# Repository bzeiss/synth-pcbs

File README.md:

# synth-pcbs
This site contains some stuff I have built for some synths/samplers I own.

I tinker with electronics, release stuff when I feel like it and I make it public when it's maybe not perfect. I'm not an electronics expert, so I may not always know what I'm doing. I learn the necessary electronics as I use it. Use at your own risk.

Be smart. Don't just trust the stuff I offer for download here. Take a look at the schematic and the PCB design beforehand.

Feedback is always very welcome 😄 Feel free to ask question in the [discussions](https://github.com/bzeiss/synth-pcbs/discussions).

***

The main content of this site (descriptions, documentations) can be found **[in the Wiki](https://github.com/bzeiss/synth-pcbs/wiki)**.

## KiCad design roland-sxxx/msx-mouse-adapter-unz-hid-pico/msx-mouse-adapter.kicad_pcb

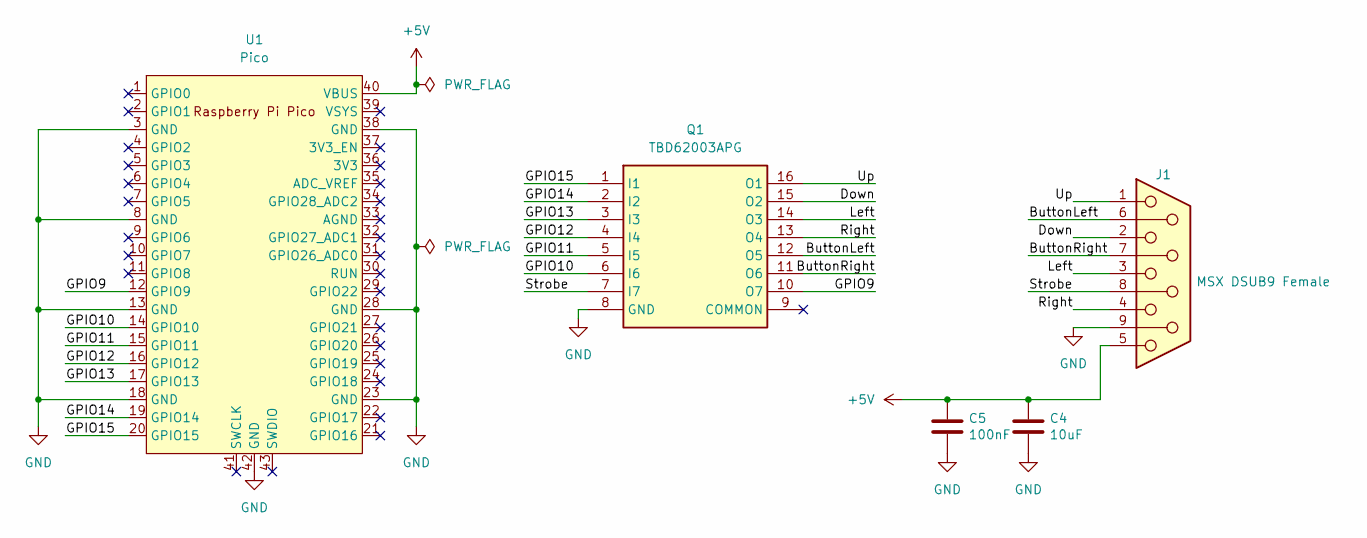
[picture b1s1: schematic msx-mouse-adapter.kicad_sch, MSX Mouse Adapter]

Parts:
C4: 10uF; C_0805_2012Metric_Pad1.18x1.45mm_HandSolder; LCSC C15850
C5: 100nF; C_0805_2012Metric_Pad1.18x1.45mm_HandSolder; LCSC C1525
J1: MSX DSUB9 Female
Q1: TBD62003APG; DIP762W60P254L1975H445Q16N; Mouser Part Number 757-TBD62003APG
U1: Pico; RPi_Pico_SMD_TH

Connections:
+5V: C4.1, C5.1, J1.5, U1.40 (VBUS)
/ButtonLeft: J1.6, Q1.12 (O5)
/ButtonRight: J1.7, Q1.11 (O6)
/Down: J1.2, Q1.15 (O2)
/GPIO9: Q1.10 (O7), U1.12 (GPIO9)
/GPIO10: Q1.6 (I6), U1.14 (GPIO10)
/GPIO11: Q1.5 (I5), U1.15 (GPIO11)
/GPIO12: Q1.4 (I4), U1.16 (GPIO12)
/GPIO13: Q1.3 (I3), U1.17 (GPIO13)
/GPIO14: Q1.2 (I2), U1.19 (GPIO14)
/GPIO15: Q1.1 (I1), U1.20 (GPIO15)
/Left: J1.3, Q1.14 (O3)
/Right: J1.4, Q1.13 (O4)
/Strobe: J1.8, Q1.7 (I7)
/Up: J1.1, Q1.16 (O1)
GND: C4.2, C5.2, J1.9, Q1.8 (GND), U1.3 (GND), U1.8 (GND), U1.13 (GND), U1.18 (GND), U1.23 (GND), U1.28 (GND), U1.38 (GND), U1.42 (GND)

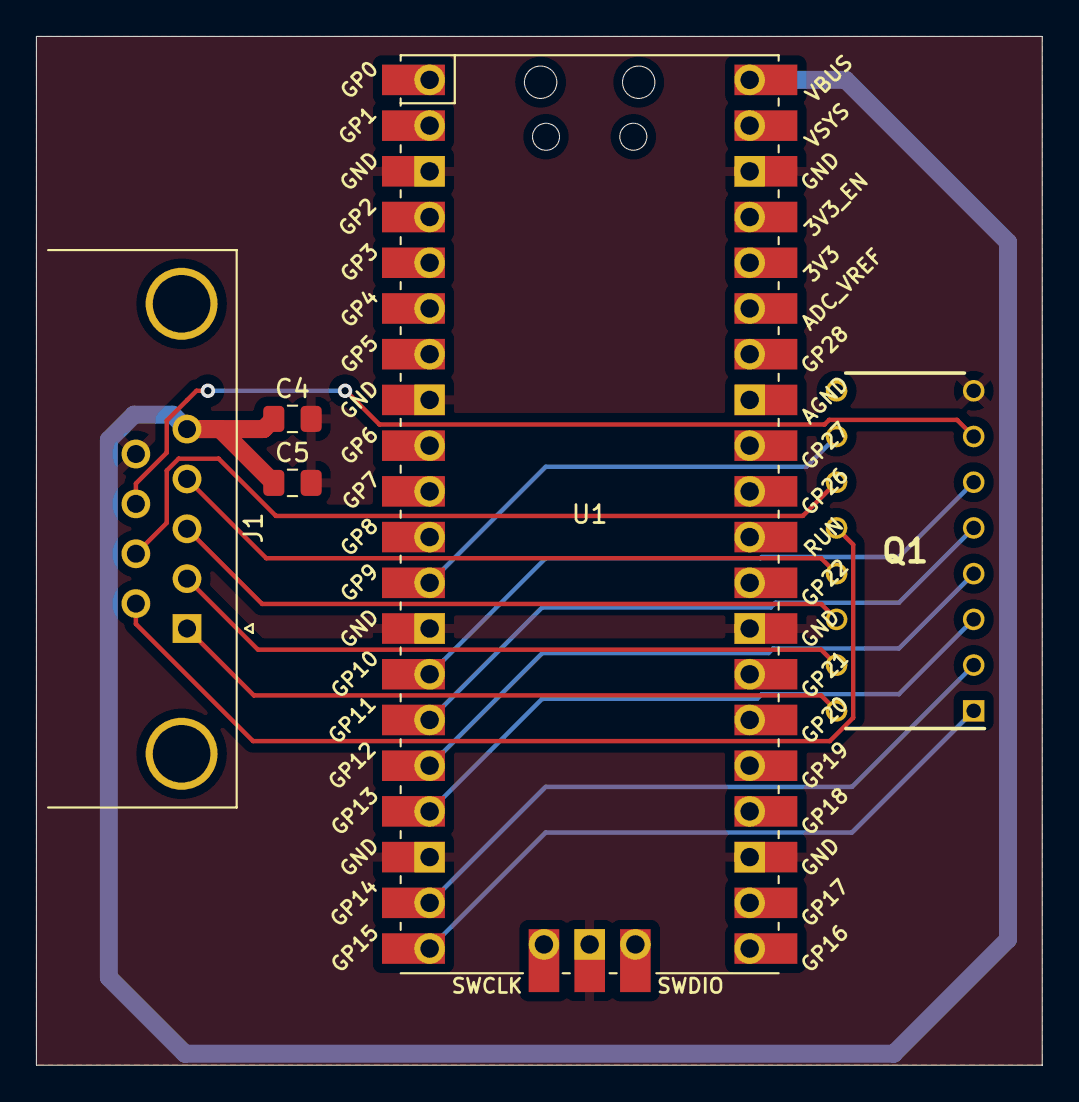
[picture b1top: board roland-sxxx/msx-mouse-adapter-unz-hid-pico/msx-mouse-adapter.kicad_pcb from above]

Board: 2 copper layers, 55.9 x 57.1 mm, 5 parts (0 on the bottom side), 16 nets.

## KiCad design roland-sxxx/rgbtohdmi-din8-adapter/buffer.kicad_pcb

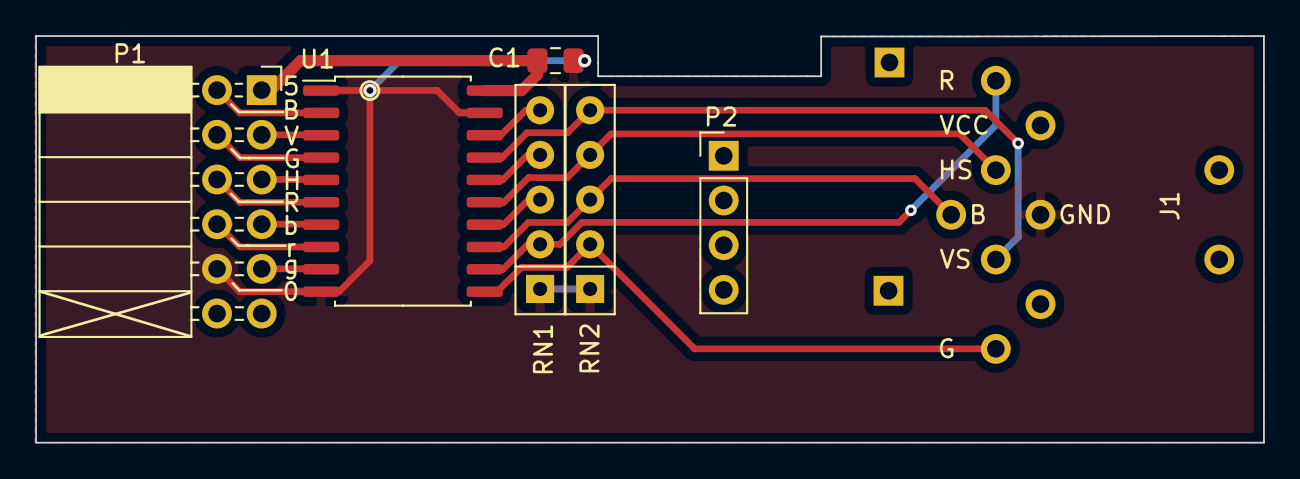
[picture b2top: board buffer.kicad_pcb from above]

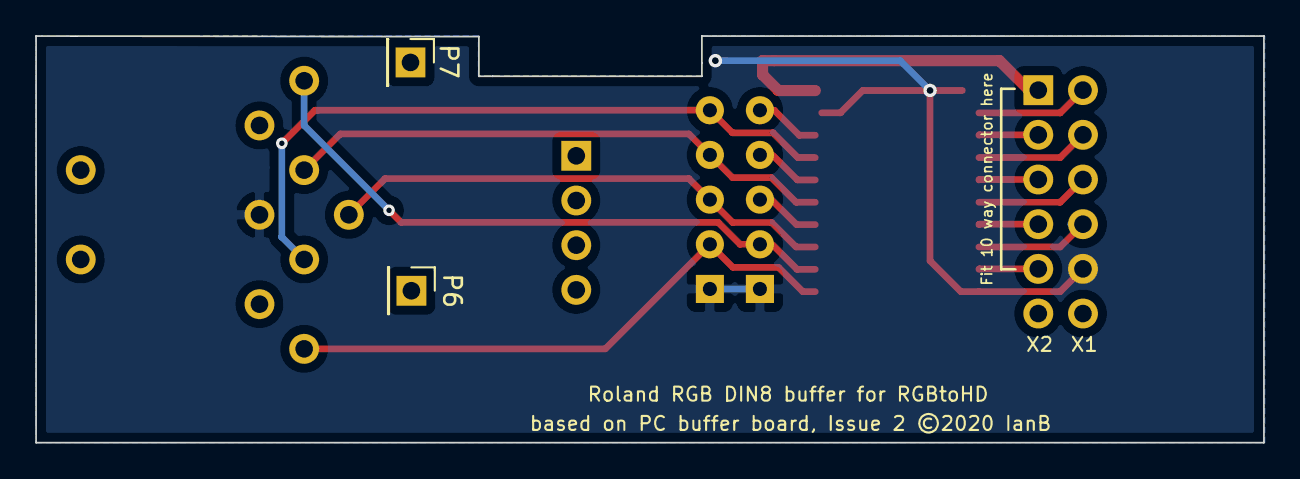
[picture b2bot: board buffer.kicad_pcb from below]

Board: 2 copper layers, 69.8 x 23.1 mm, 9 parts (2 on the bottom side), 18 nets.

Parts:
C1: 100n; C_0805_2012Metric_Pad1.15x1.40mm_HandSolder
J1: DIN-8 Female (Symbol has 2 and 8 swapped!); DIN8_5211511-1
P1: Conn_02x06_Odd_Even; PinSocket_2x06_P2.54mm_Horizontal
P2: Conn_01x04; PinHeader_1x04_P2.54mm_Vertical
P6, P7: Conn_01x01; PinHeader_1x01_P2.54mm_Vertical
RN1, RN2: 470R; R_Array_SIP5
U1: 74LS245; SOIC-20W_7.5x12.8mm_P1.27mm

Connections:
/B2: P1.7, U1.7
/B3: P1.2, U1.2
/G2: P1.9, U1.9
/G3: P1.4, U1.4
/GND: C1.1, J1.2, P1.10, RN1.1, RN2.1, U1.1, U1.10, U1.19
/I_B2: J1.8, RN2.3, U1.13
/I_B3: RN1.5, U1.18
/I_G2: J1.7, RN2.2, U1.11
/I_G3: RN1.4, U1.16
/I_R2: J1.6, RN1.2, U1.12
/I_R3: RN1.3, U1.14
/I_SYNC: J1.4, RN2.4, U1.15
/I_VSYNC: J1.5, RN2.5, U1.17
/R2: P1.8, U1.8
/R3: P1.6, U1.6
/SYNC: P1.5, U1.5
/VCC: C1.2, P1.1, U1.20
/VSYNC: P1.3, U1.3

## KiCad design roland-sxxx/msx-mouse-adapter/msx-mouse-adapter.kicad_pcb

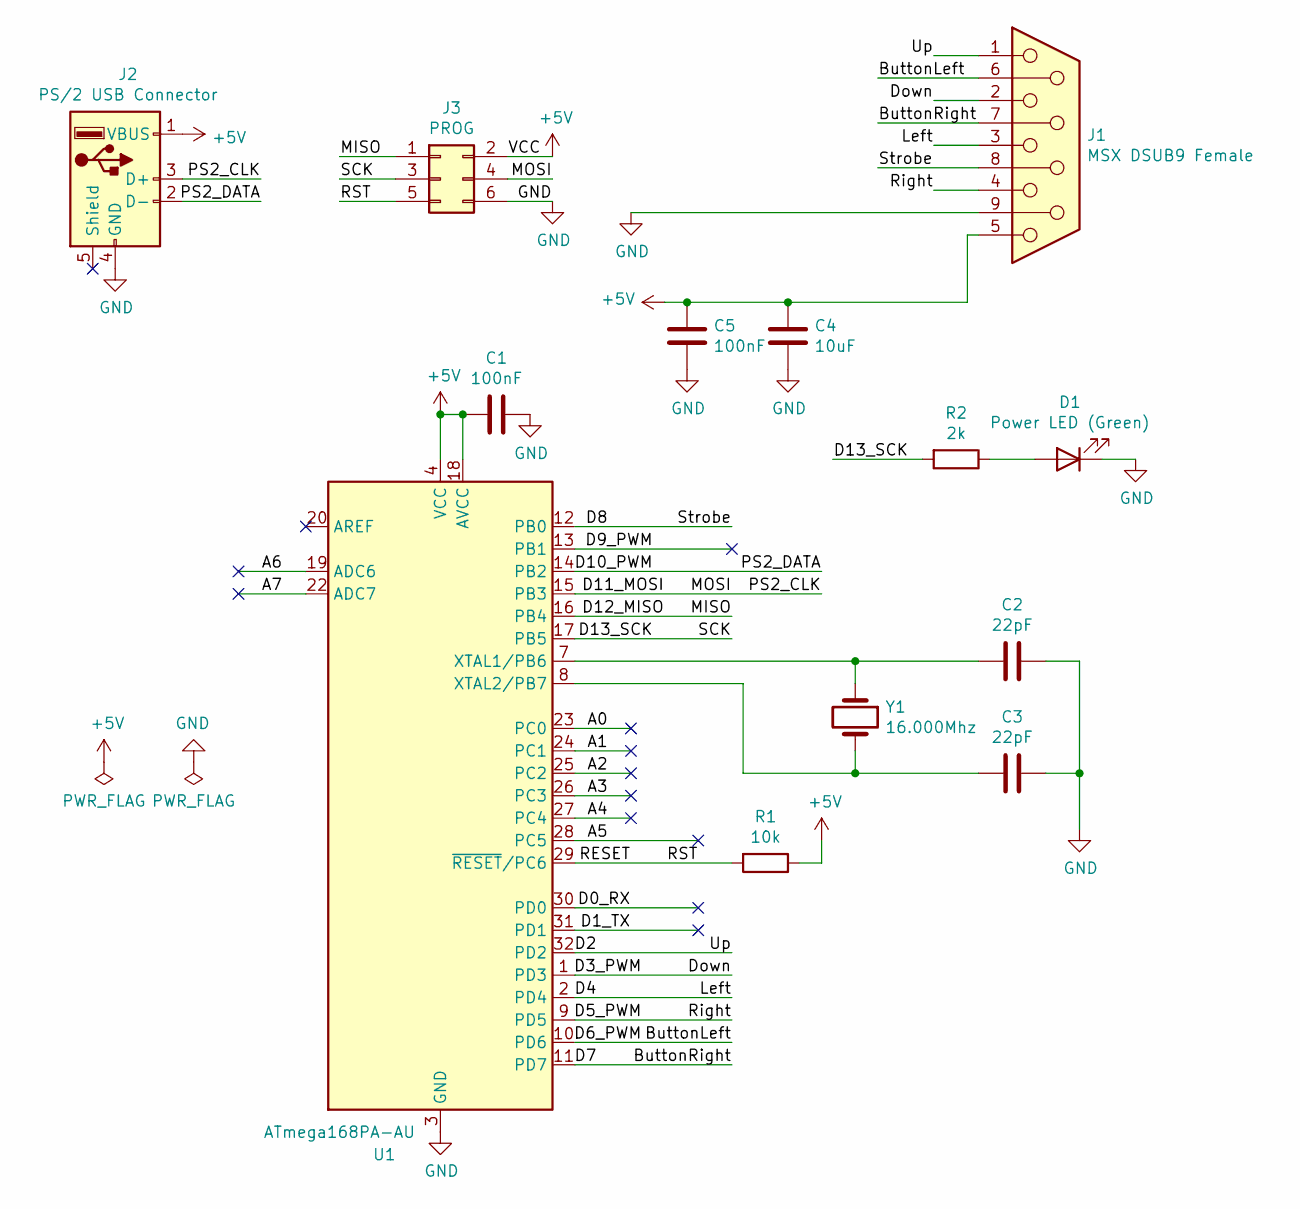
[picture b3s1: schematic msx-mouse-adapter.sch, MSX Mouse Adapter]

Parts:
C1, C5: 100nF; C_0805_2012Metric_Pad1.18x1.45mm_HandSolder; LCSC C1525
C2, C3: 22pF; C_0805_2012Metric_Pad1.18x1.45mm_HandSolder; LCSC C1555
C4: 10uF; C_0805_2012Metric_Pad1.18x1.45mm_HandSolder; LCSC C15850
D1: Power LED (Green); LED_0805_2012Metric_Pad1.15x1.40mm_HandSolder; LCSC C917188
J1: MSX DSUB9 Female
J2: PS/2 USB Connector; USB_A_Molex_67643_Horizontal
J3: PROG; PinHeader_2x03_P2.54mm_Vertical
R1: 10k; R_0805_2012Metric_Pad1.20x1.40mm_HandSolder; LCSC C25744
R2: 2k; R_0805_2012Metric_Pad1.20x1.40mm_HandSolder; LCSC C4109
U1: ATmega168PA-AU; TQFP-32_7x7mm_P0.8mm; LCSC C8728
Y1: 16.000Mhz; Crystal_SMD_7050-4Pin_7.0x5.0mm

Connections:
+5V: C1.2, C4.1, C5.1, J1.5, J2.1 (VBUS), J3.2, R1.1, U1.4 (VCC), U1.6 (VCC), U1.18 (AVCC)
/A0: U1.23 (PC0)
/A1: U1.24 (PC1)
/A2: U1.25 (PC2)
/A3: U1.26 (PC3)
/A4: U1.27 (PC4)
/A5: U1.28 (PC5)
/A6: U1.19 (ADC6)
/A7: U1.22 (ADC7)
/ButtonLeft: J1.6, U1.10 (PD6)
/ButtonRight: J1.7, U1.11 (PD7)
/D0_RX: U1.30 (PD0)
/D1_TX: U1.31 (PD1)
/D2: J1.1, U1.32 (PD2)
/D3_PWM: J1.2, U1.1 (PD3)
/D4: J1.3, U1.2 (PD4)
/D5_PWM: J1.4, U1.9 (PD5)
/D8: J1.8, U1.12 (PB0)
/D9_PWM: U1.13 (PB1)
/D10_PWM: J2.2 (D-), U1.14 (PB2)
/D11_MOSI: J2.3 (D+), J3.4, U1.15 (PB3)
/D12_MISO: J3.1, U1.16 (PB4)
/D13_SCK: J3.3, R2.2, U1.17 (PB5)
/RESET: J3.5, R1.2, U1.29 (~RESET~/PC6)
GND: C1.1, C2.2, C3.2, C4.2, C5.2, D1.1 (K), J1.9, J2.4 (GND), J3.6, U1.3 (GND), U1.5 (GND), U1.21 (GND)
unnamed: C2.1, U1.7 (XTAL1/PB6), Y1.1
unnamed: C3.1, U1.8 (XTAL2/PB7), Y1.2
unnamed: D1.2 (A), R2.1

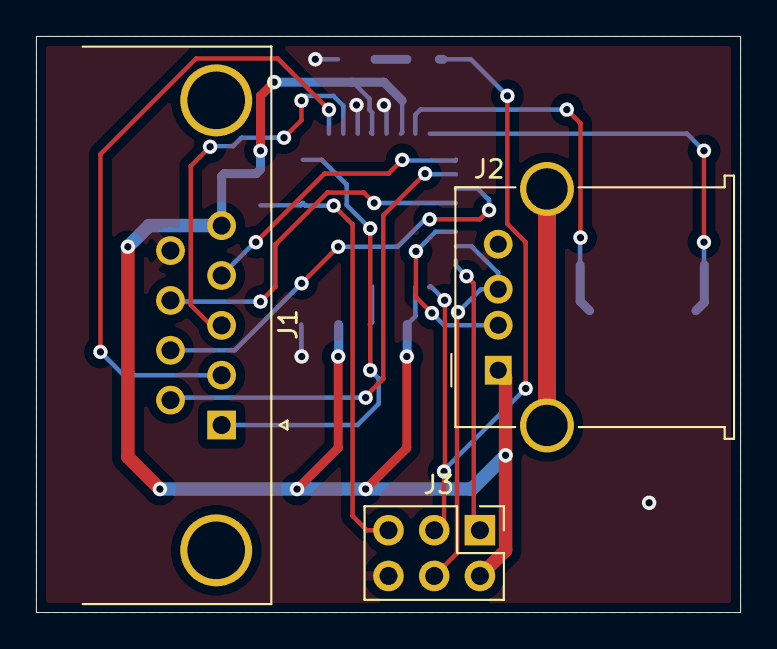
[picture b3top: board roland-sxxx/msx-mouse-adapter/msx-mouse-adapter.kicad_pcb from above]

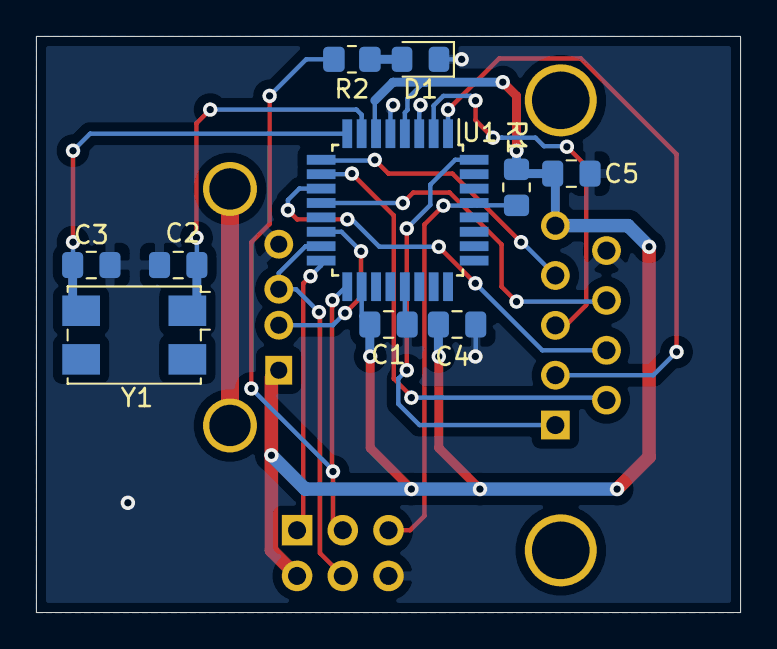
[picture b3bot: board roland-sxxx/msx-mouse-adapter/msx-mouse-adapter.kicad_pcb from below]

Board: 2 copper layers, 39.1 x 32.0 mm, 13 parts (10 on the bottom side), 17 nets.

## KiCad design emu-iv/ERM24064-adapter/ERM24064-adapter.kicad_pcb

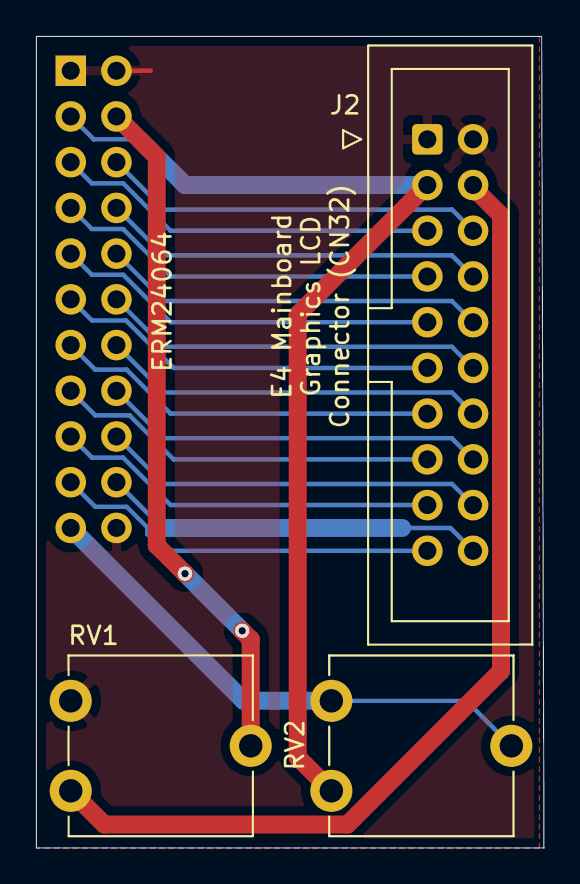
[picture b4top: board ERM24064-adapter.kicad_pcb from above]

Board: 2 copper layers, 28.2 x 45.1 mm, 4 parts (1 on the bottom side), 21 nets.

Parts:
J1: ERM24064-1-display; PinSocket_2x11_P2.54mm_Vertical
J2: ERM24064-1-mainboard; IDC-Header_2x10_P2.54mm_Vertical
RV1: Trimpot 10k; Potentiometer_ACP_CA9-V10_Vertical
RV2: Trimpot 1k; Potentiometer_ACP_CA9-V10_Vertical

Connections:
+5V: J1.3, J2.3, RV2.1
C_D: J1.8, J2.8
DB0: J1.11, J2.11
DB1: J1.12, J2.12
DB2: J1.13, J2.13
DB3: J1.14, J2.14
DB4: J1.15, J2.15
DB5: J1.16, J2.16
DB6: J1.17, J2.17
DB7: J1.18, J2.18
FS: J1.19, J2.19
LED_A: J1.21, RV2.2, RV2.3
LED_K: J1.1, J1.2, J1.22, J2.1, J2.2, RV1.3
NC: J1.9, J2.9
unnamed: J1.4, RV1.2
V0: J2.4, RV1.1
VOUT: J1.20, J2.20
~CE: J1.7, J2.7
~RD: J1.6, J2.6
~RST: J1.10, J2.10
~WR: J1.5, J2.5

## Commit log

2021-07-15 initial version with molex
2021-07-15 direct connection
2021-07-15 correction wrt. to the current limiting resistor for the backlight led.
2021-07-15 removed the rescue lib.
2021-07-28 removed old adapter version with extra backlight connector. not necessary.
2021-07-28 direct adapter is the new main adapter.
2021-07-28 schematic and pcblayout
2021-10-31 initial version of a more compact roland sxx msx adapter.
2021-10-31 correction of label placement
2021-11-06 patched arduino software.
2021-11-06 made the mouse adapter more compact.
2021-11-21 added initial version of rgbtohdmi din8 buffer board for roland samplers.
2021-12-03 holes of the gerber were too small.
2024-02-18 Fixed profile.
2024-04-03 quick prototype board for the uniz-hid-pico project.

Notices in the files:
roland-sxxx/rgbtohdmi-din8-adapter/buffer.kicad_pcb:
based on PC buffer board, Issue 2 ©2020 IanB
